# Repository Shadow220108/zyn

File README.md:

<h1 align="center">
<br>

<br>
zyn
<br>
</h1>

<h3 align="center">

A 16 by 8 RGB LED matrix on an ESP32-C3, with a mic, two buttons and USB-C charging!

</h3>

<div align="center">

| Back render |
| --- |
|  |

</div>

## Specs

| | |
| --- | --- |
| Board | 127 x 92 mm, 4 layers |
| Pixels | 128 x SK6812 mini-e, 16 columns by 8 rows, on the bottom side |
| MCU | ESP32-C3-WROOM-02 (4 MB flash, wifi, BLE 5, PCB antenna) |
| Mic | ICS-43434 on I2S (wired, not used by the firmware yet) |
| Charger | MCP73831, 1S LiPo, 500 mA, JST PH connector |
| Regulator | AP2112K-3.3 for the logic |
| Matrix supply | VLED, from VSYS through a p-channel load switch, enabled by IO4 |
| Inputs | BTN_A (boot), BTN_B, reset |
| Status | red charge LED (D2), blue LED on IO8 (D3) |

## How it works

USB-C comes in through a 2A polyfuse (F1). The charger takes VBUS and charges the LiPo, and VSYS feeds the 3.3 V regulator and the matrix switch. The matrix only gets power when IO4 is high, so the board can switch the LEDs off when it's idle.

The data line runs from IO10 through an SN74LV1T125 level shifter (powered from VLED, so the pixels get a logic level they can read) and a 33 ohm series resistor, into the first pixel's DIN. The 128 pixels are chained DIN to DOUT in a snake: row 0 runs left to right, row 1 runs right to left, and so on.

## Pinout

| GPIO | Module pin | Net | Used for |
| --- | --- | --- | --- |
| IO10 | 10 | LED_DATA | pixel data (through the level shifter) |
| IO4 | 3 | LED_EN | matrix power on/off |
| IO9 | 8 | BTN_A | boot button, cycles effects |
| GPIO20 (RXD) | 11 | BTN_B | user button, cycles brightness |
| IO8 | 7 | IO8_LED | blue status LED (D3) |
| IO5 / IO6 / IO7 | 4 / 5 / 6 | MIC_WS / MIC_SCK / MIC_SD | mic (I2S, not used yet) |
| IO18 / IO19 | 13 / 14 | USB_D- / USB_D+ | native USB |
| IO3 / IO1 | 15 / 17 | CC2_SENSE / CC1_SENSE | USB-C orientation sense |
| IO0 | 18 | VBAT_SENSE | battery voltage sense |
| IO2 | 16 | IO2 | spare |

## Firmware

The firmware is in [firmware/zyn/zyn.ino](firmware/zyn/zyn.ino). It was written with help from AI. The pins were checked against the netlist and the module pin layout, but this exact file has not been run on the board yet, so test it with the matrix at low brightness first.

### Setup

1. Arduino IDE, Preferences, add the ESP32 board manager URL `https://espressif.github.io/arduino-esp32/package_esp32_index.json`
2. Boards Manager: install "esp32" by Espressif
3. Library Manager: install "FastLED"
4. Board: "ESP32C3 Dev Module", and turn on "USB CDC on boot" if you want serial output
5. Hold BOOT while plugging in the first time, then upload `zyn.ino`

### Controls

| Button | Action |
| --- | --- |
| BTN_A (boot) | cycle effects: rainbow, scan line, sparkle, breathe |
| BTN_B | cycle brightness: low, medium, high |

The status LED blinks once a second while the firmware is running.

### Notes

- The matrix runs from VSYS, so on battery the pixels see 3.0 to 4.2 V. The brightness is capped at 50 and the power limit is set to 400 mA in the code. Check the pixels at battery voltage before you go higher.
- The chain order and the pixel grid come from the netlist and the position file, so every pixel is in the right place for the effects.
- The mic is wired but the firmware doesn't read it yet.

## Schematic

<div align="center">

| Schematic overview |
| --- |
|  |

</div>

## PCB

<div align="center">

| Full board |
| --- |
|  |

</div>

## How can you get one?

All the files you need are in the `production` folder. Upload `production/zyn.zip` to any PCB fab, and use `production/zyn_bom.csv` and the position files for assembly. The full build log is in [JOURNAL.md](JOURNAL.md).

## BOM

Full part list with LCSC part numbers is in [BOM.csv](BOM.csv) and [production/zyn_bom.csv](production/zyn_bom.csv).

| Designator | Footprint | Qty | Value | LCSC part | Unit price (INR) | Line total (INR) |
| --- | --- | --- | --- | --- | --- | --- |
| C1, C2 | 0603 | 2 | 4.7u/10V | CL10A475KO8NNNC | 10 | 20 |
| C10, C4, C6 | 0402 | 3 | 1u/10V | CL05A105KP5NNNC | 2 | 6 |
| C101 to C228 | 0402 | 132 | 100n/16V | CL05B104KO5NNNC | 1 | 132 |
| C12 | 0402 | 1 | 47n/16V | CL05B473KO5NNNC | 2 | 2 |
| C13, C14 | 1206 | 2 | 47u/10V | CL31A476MPHNNNE | 25 | 50 |
| C15, C16, C3, C5 | 0805 | 4 | 22u/10V | CL21A226MPQNNNE | 12 | 48 |
| C8 | 0603 | 1 | 10u/10V | CL10A106KP8NNNC | 5 | 5 |
| D1 | D_SMA | 1 | SS34 | SS34 (3 A / 40 V) | 10 | 10 |
| D2 | 0603 | 1 | RED (charging) | KT-0603R | 3 | 3 |
| D3 | 0603 | 1 | BLUE (IO8) | KT-0603B | 3 | 3 |
| D101 to D228 | SK6812MINI-E reverse mount | 128 | SK6812MINI-E | SK6812MINI-E | 20 | 2560 |
| F1 | 1812 | 1 | 2A | Bourns MF-MSMF200-2 | 15 | 15 |
| J1 | USB-C HRO TYPE-C-31-M-12 | 1 | USB-C | HRO TYPE-C-31-M-12 | 25 | 25 |
| J2 | JST PH S2B-PH-SM4-TB | 1 | LiPo 1S (JST-PH) | JST S2B-PH-SM4-TB | 10 | 10 |
| Q1, Q2 | SOT-23 | 2 | AO3401A | AO3401A | 15 | 30 |
| Q3 | SOT-23 | 1 | 2N7002 | 2N7002 | 3 | 3 |
| R1, R2 | 0402 | 2 | 5.1k | RC0402FR-075K1L | 1 | 2 |
| R10, R11, R12, R13, R14, R17, R3, R4 | 0402 | 8 | 10k | RC0402FR-0710KL | 1 | 8 |
| R15, R6 | 0402 | 2 | 1k | RC0402FR-071KL | 1 | 2 |
| R16, R18, R19, R21, R7, R8, R9 | 0402 | 7 | 100k | RC0402FR-07100KL | 1 | 7 |
| R20 | 0402 | 1 | 33R | RC0402FR-0733RL | 1 | 1 |
| R5 | 0402 | 1 | 2k | RC0402FR-072KL | 1 | 1 |
| SW1 | SW_SPDT_Shouhan_MSK12C02 | 1 | POWER (slide) | Shouhan MSK12C02 | 25 | 25 |
| SW2 | SW_SPST_PTS810 | 1 | RESET | C&K PTS810SJM250SMTRLFS | 10 | 10 |
| SW3, SW4 | SW_Push Alps SKRTLAE010 | 2 | BTN_A / BTN_B | Alps SKRTLAE010 | 15 | 30 |
| U1 | ESP32-C3-WROOM-02 | 1 | ESP32-C3-WROOM-02 | ESP32-C3-WROOM-02-N4 | 180 | 180 |
| U2 | ICS-43434 | 1 | ICS-43434 | ICS-43434 | 150 | 150 |
| U3 | SOT-23-5 | 1 | MCP73831-2-OT | MCP73831T-2ACI/OT | 25 | 25 |
| U4 | SOT-23-5 | 1 | AP2112K-3.3 | AP2112K-3.3TRG1 | 12 | 12 |
| U5 | SOT-23-5 | 1 | SN74LV1T125DBV | SN74LV1T125DBVR | 15 | 15 |
| U6 | SOT-23-6 | 1 | USBLC6-2SC6 | USBLC6-2SC6 | 10 | 10 |
| **Total** | | | | | | **3400** |

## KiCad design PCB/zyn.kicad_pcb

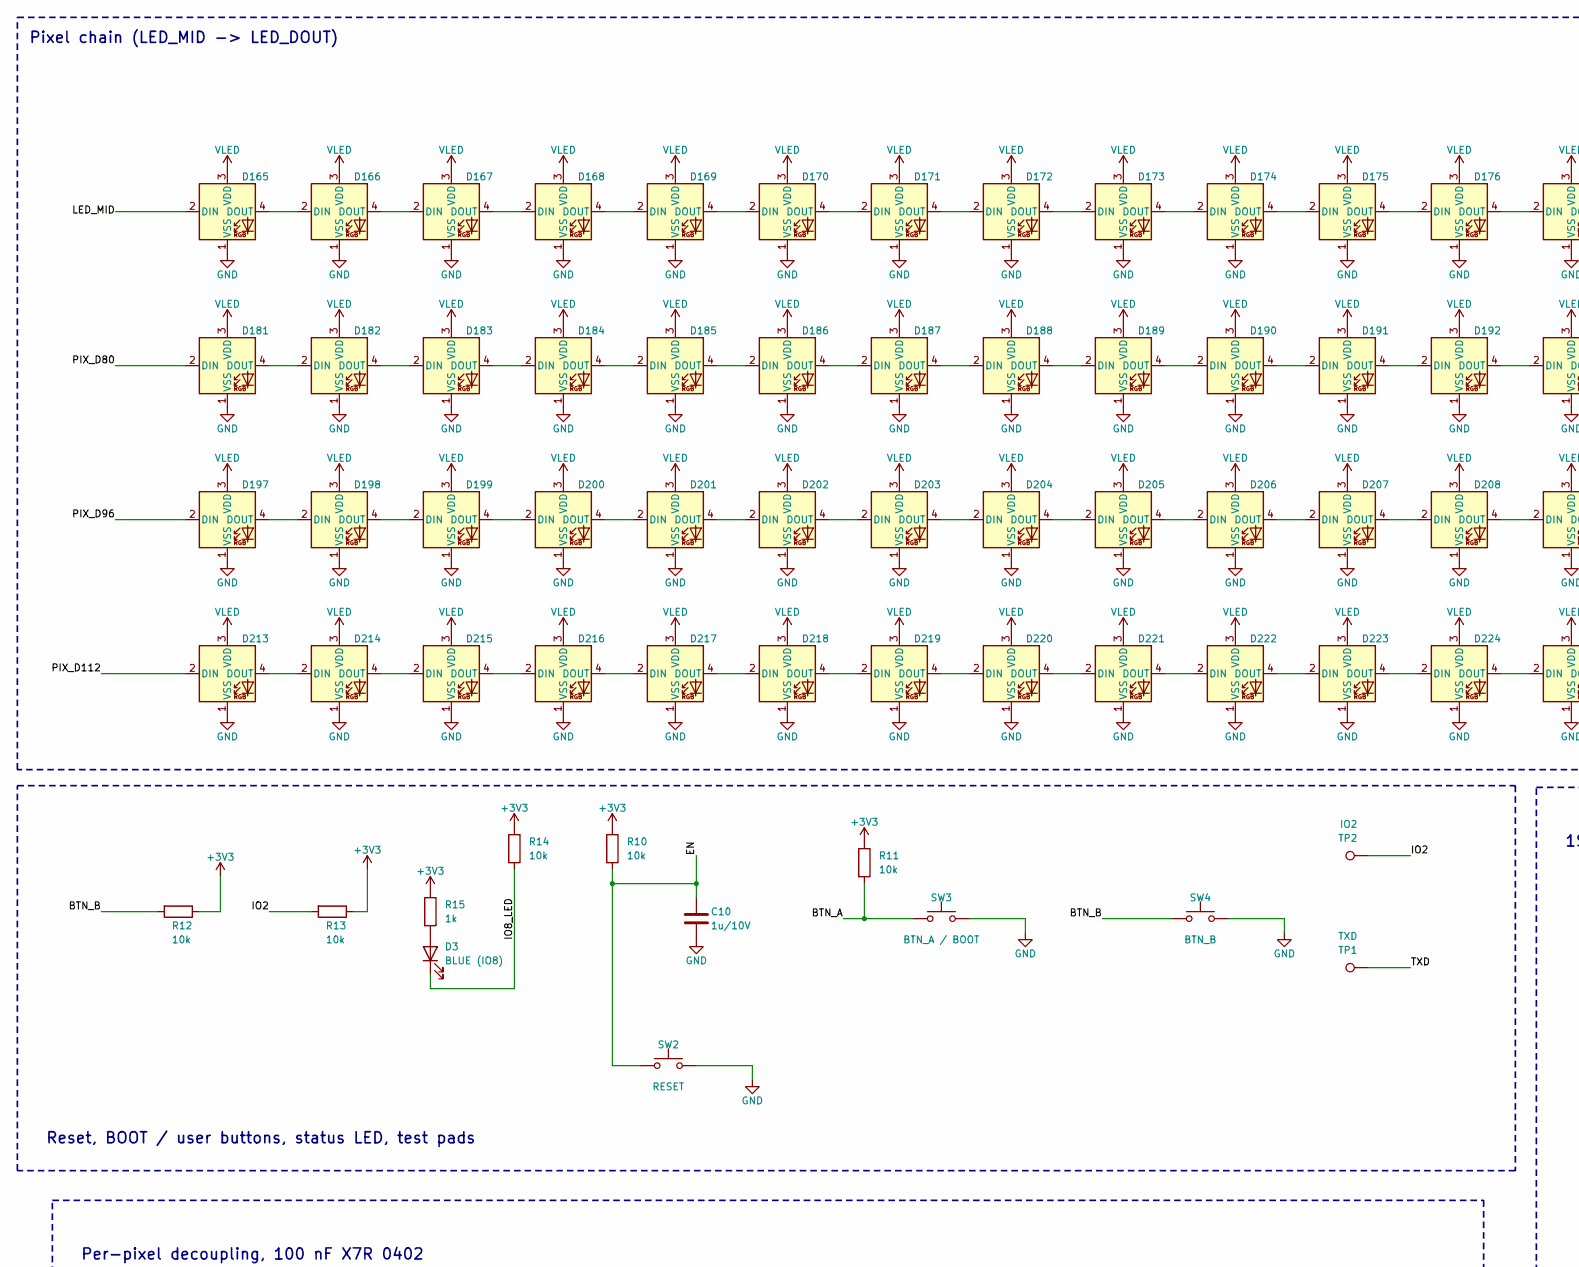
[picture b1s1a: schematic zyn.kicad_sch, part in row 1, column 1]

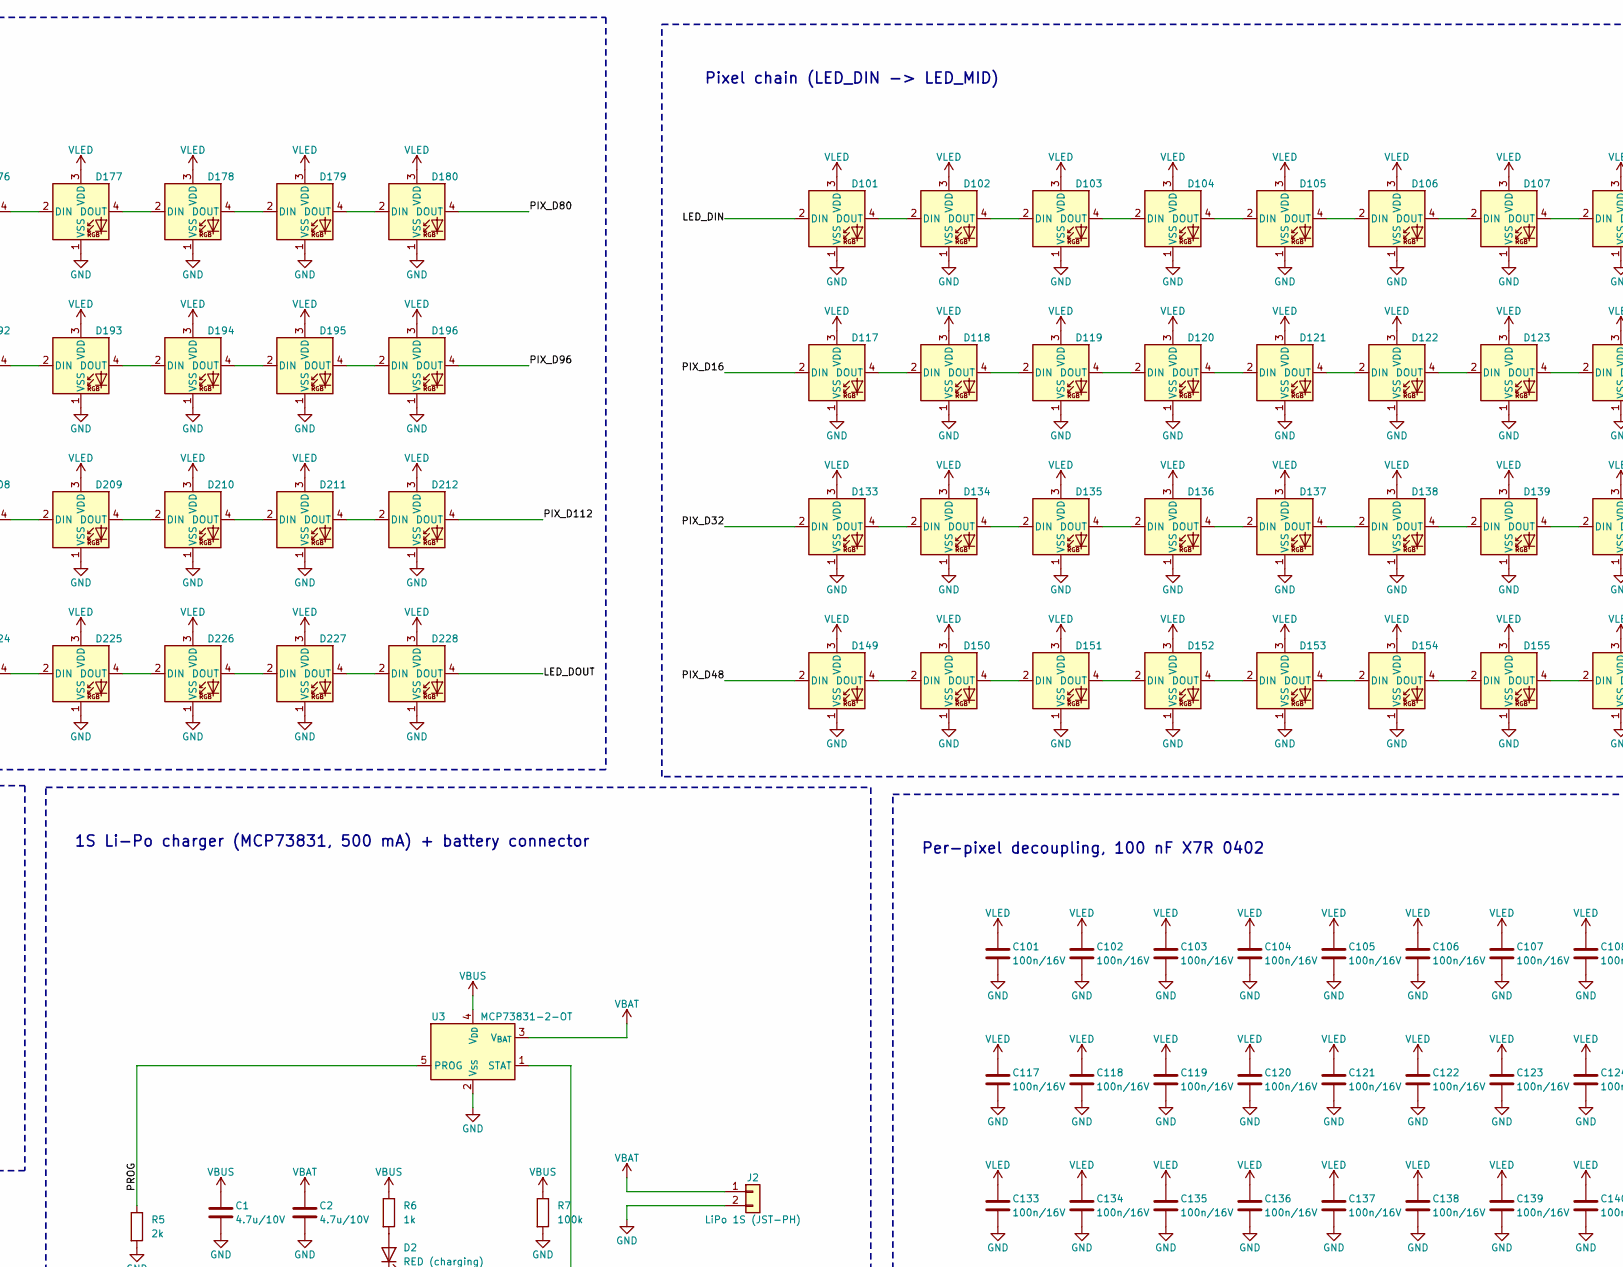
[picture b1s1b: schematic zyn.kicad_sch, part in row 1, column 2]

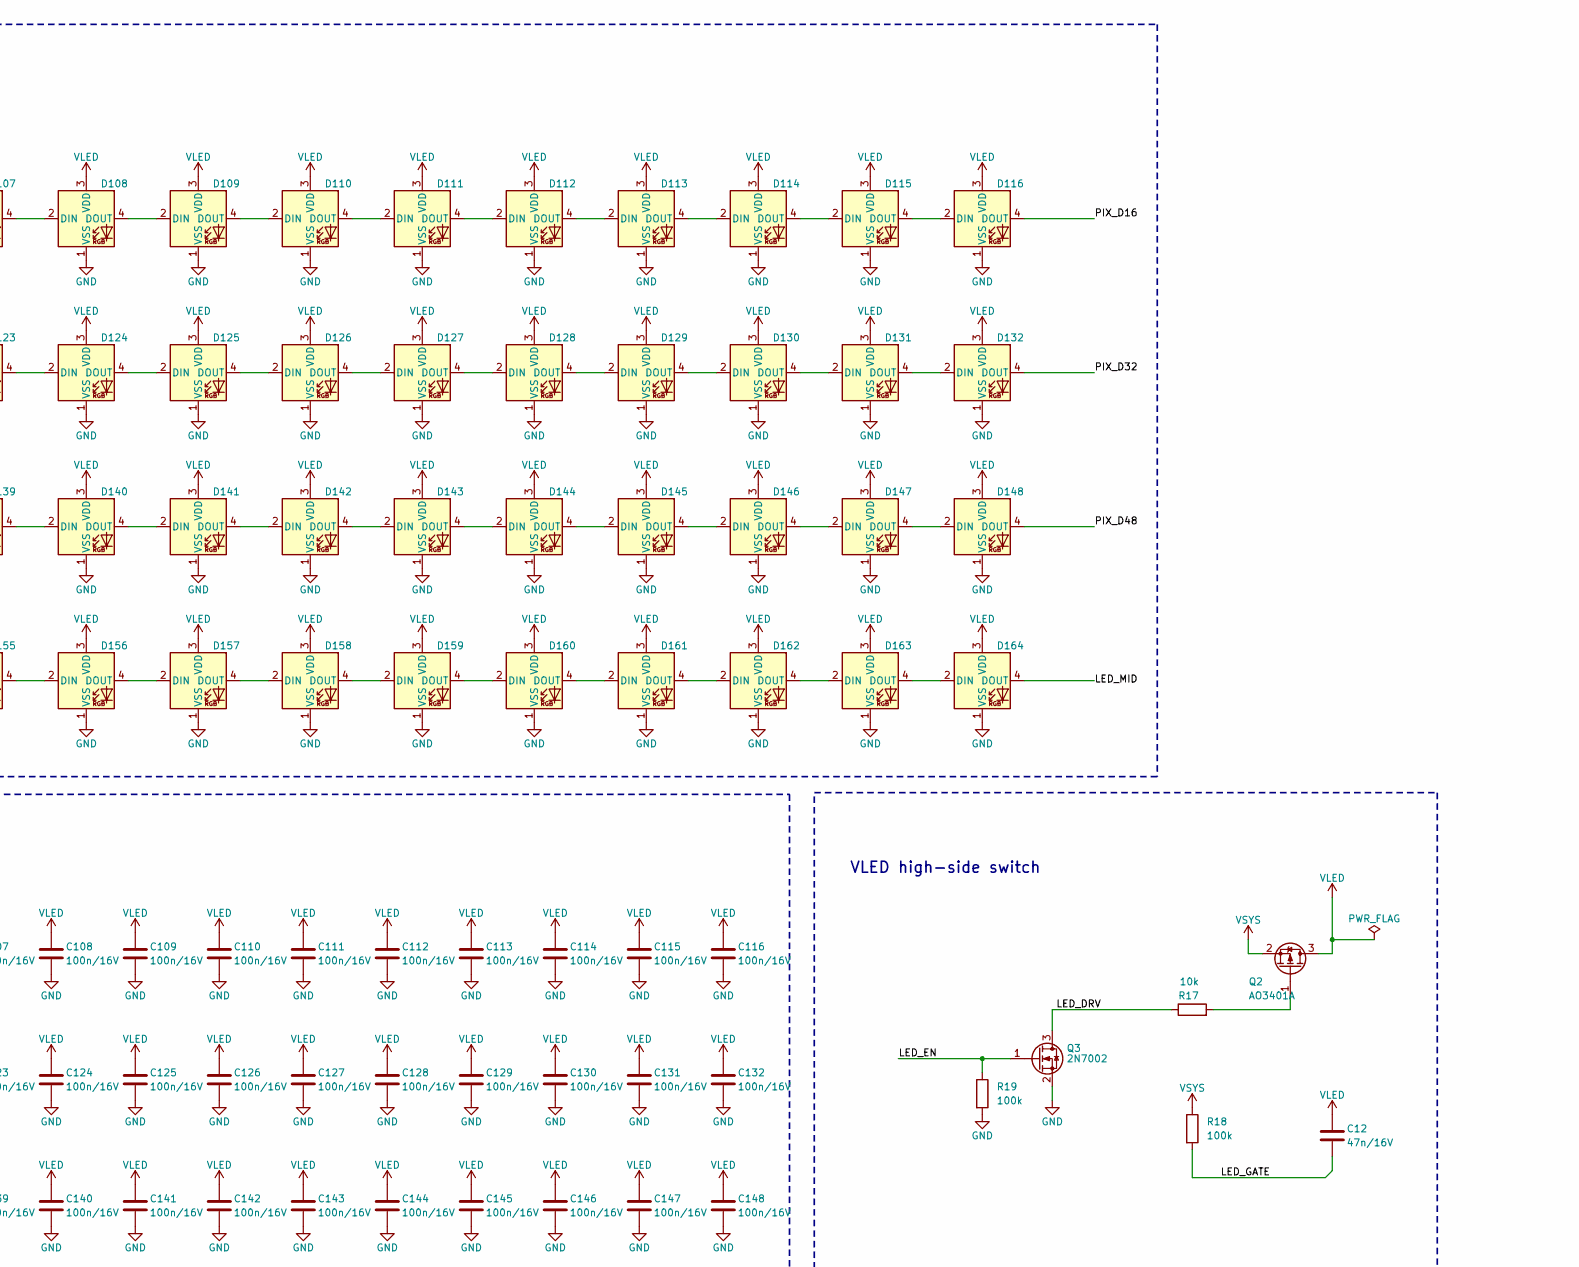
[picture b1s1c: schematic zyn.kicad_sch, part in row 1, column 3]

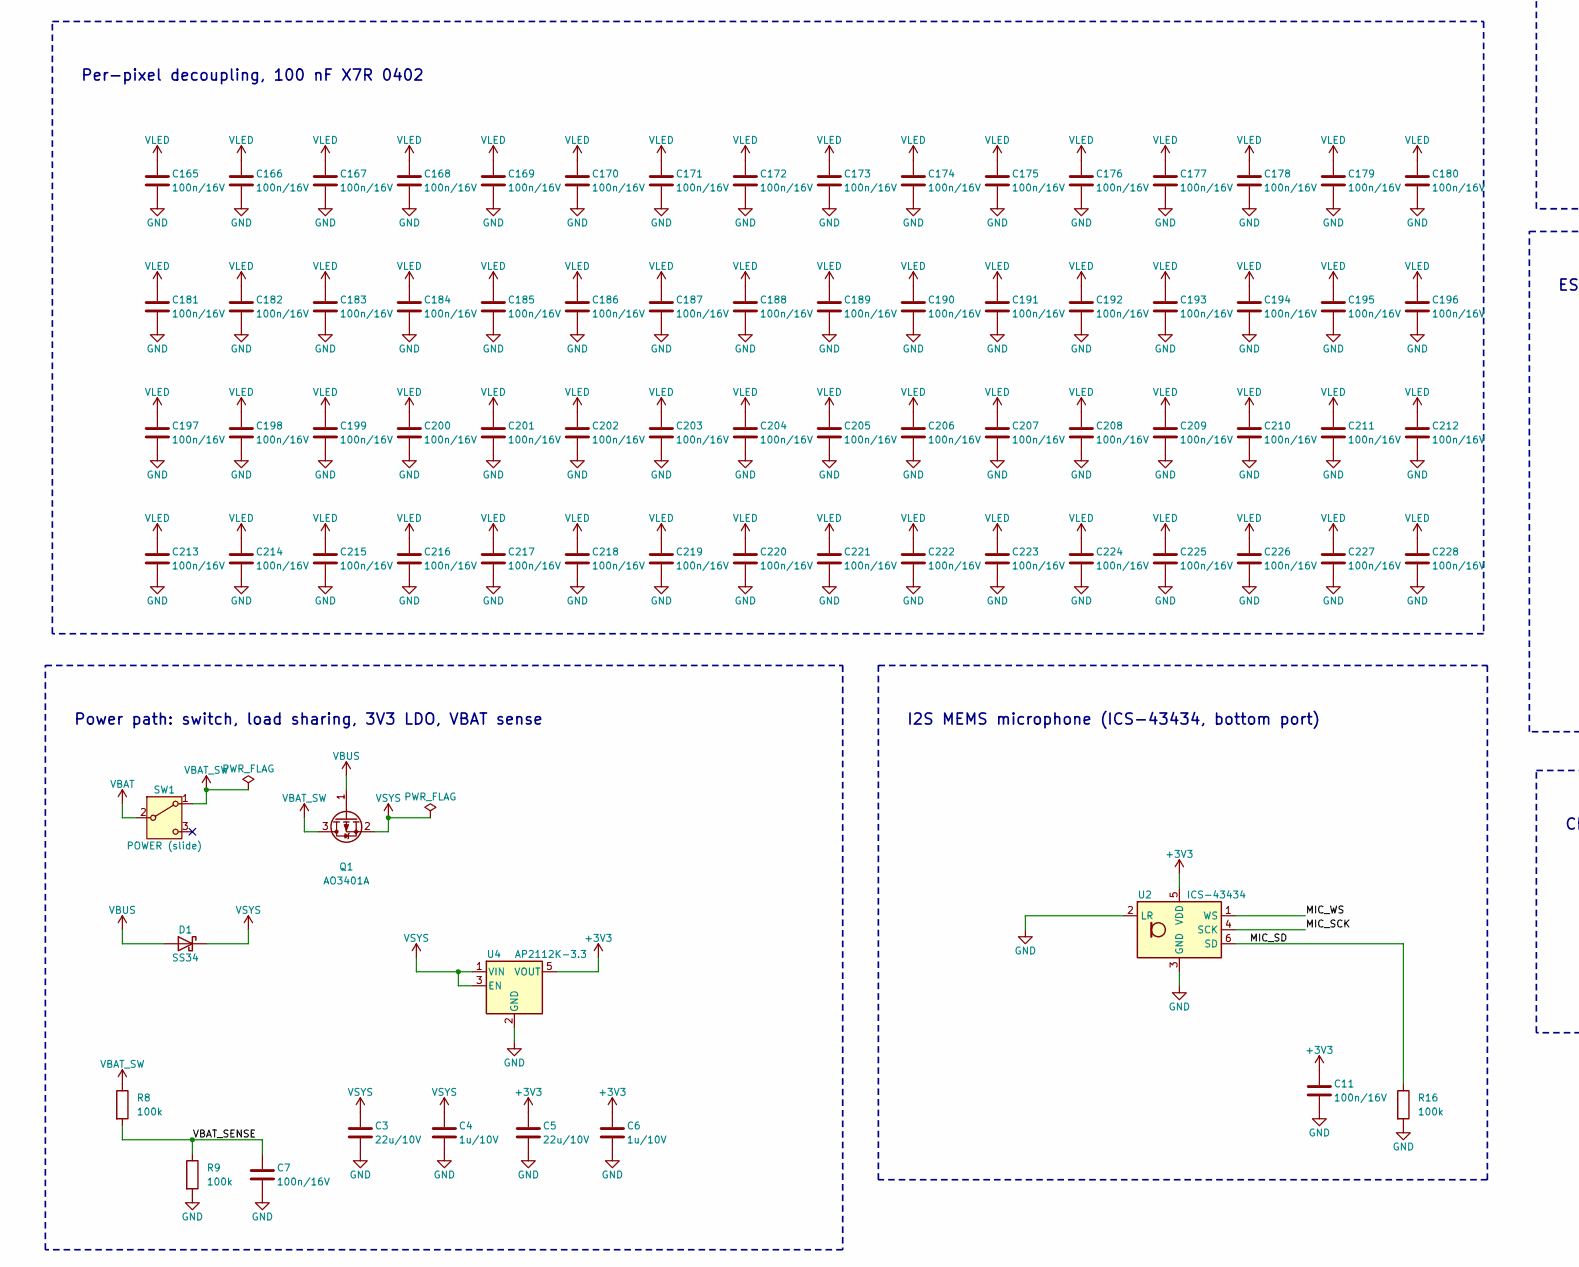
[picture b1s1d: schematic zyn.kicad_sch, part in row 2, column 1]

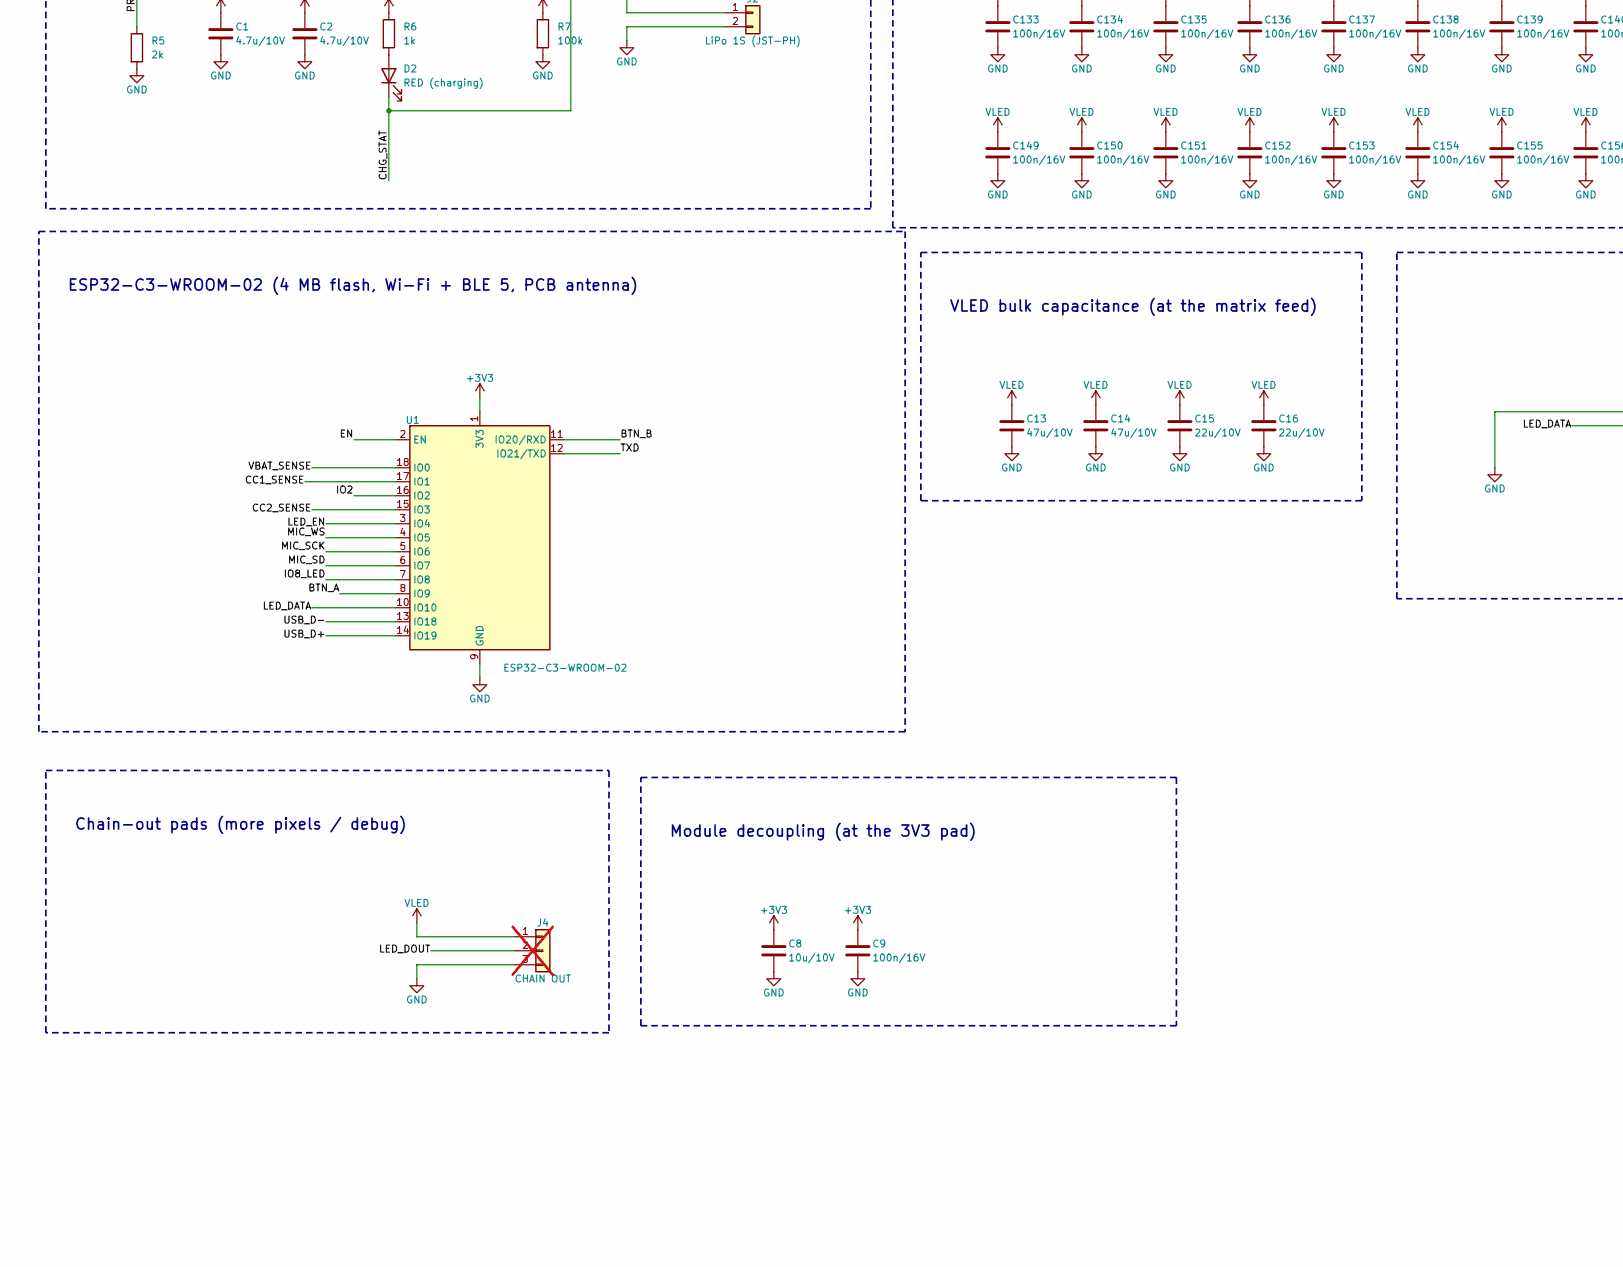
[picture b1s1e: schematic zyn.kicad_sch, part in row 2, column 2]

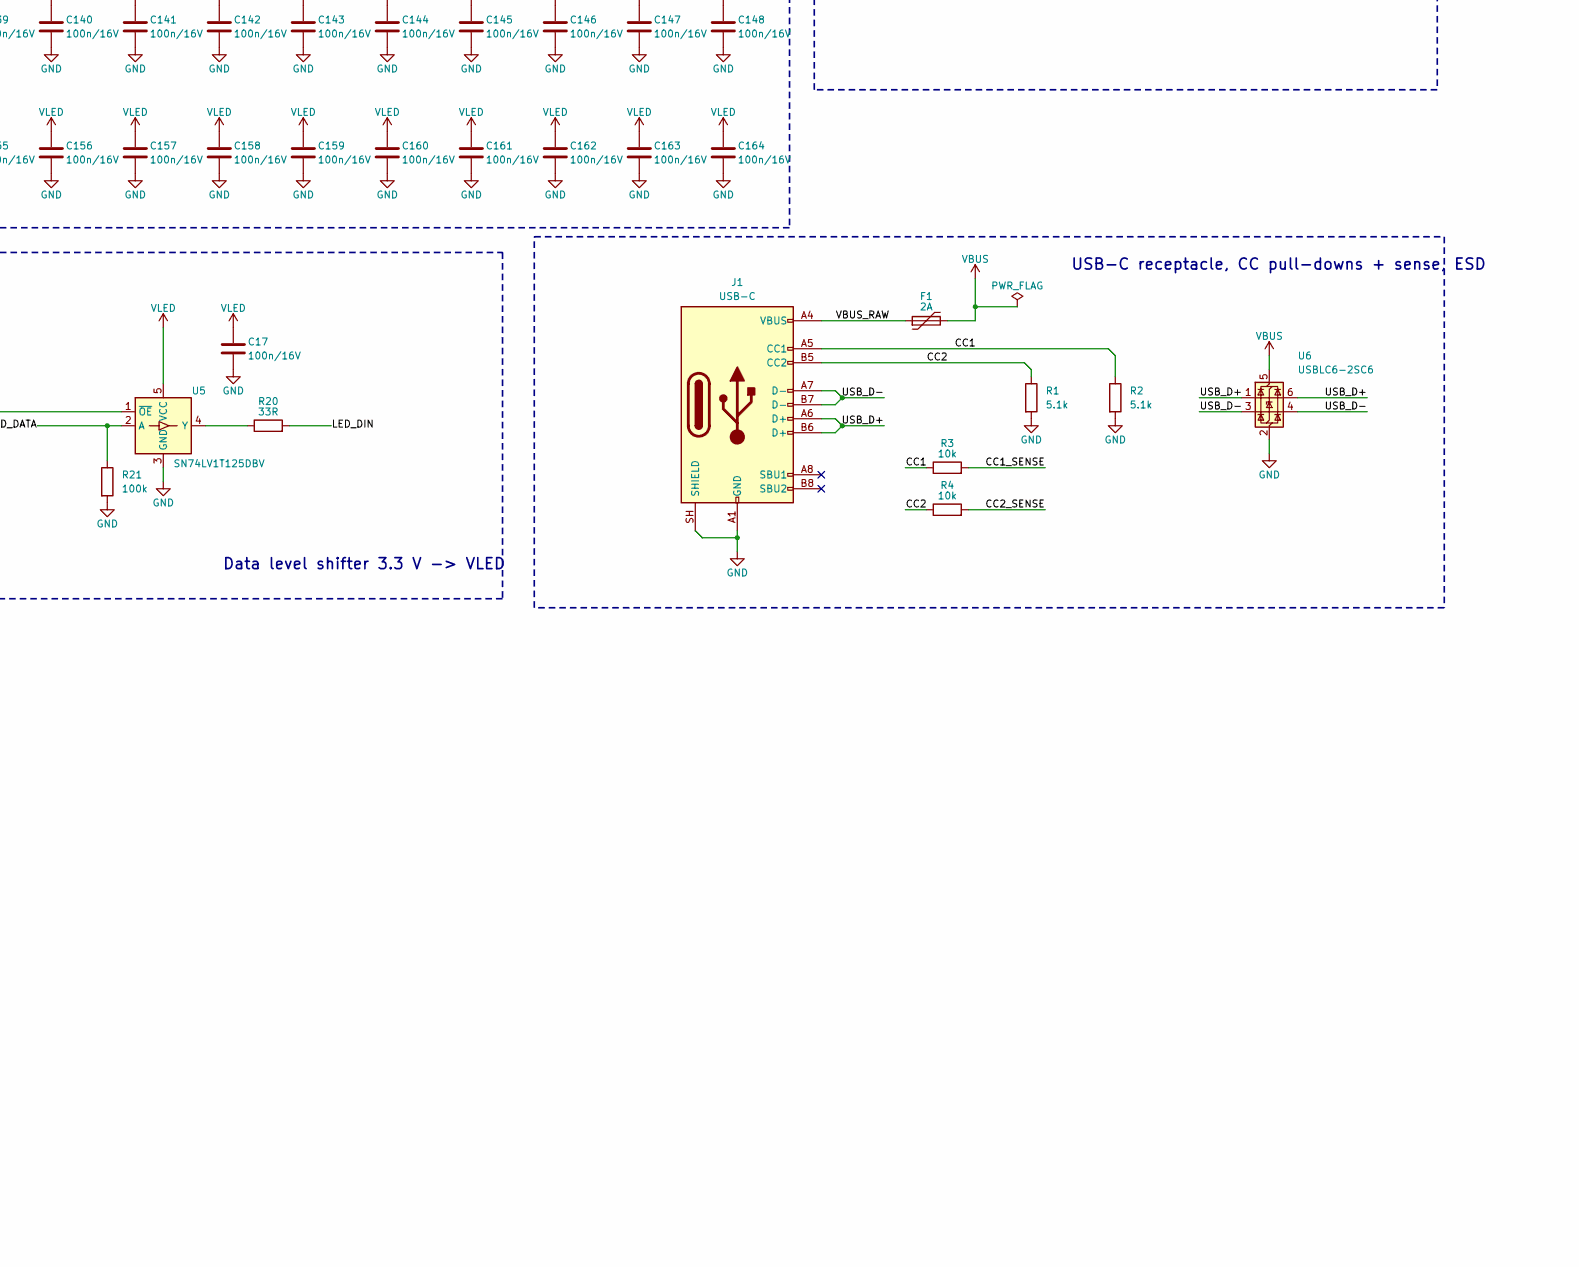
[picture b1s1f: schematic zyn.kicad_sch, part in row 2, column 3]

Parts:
C1, C2: 4.7u/10V; C_0603_1608Metric; MPN CL10A475KO8NNNC
C3, C5, C15, C16: 22u/10V; C_0805_2012Metric; MPN CL21A226MPQNNNE
C4, C6, C10: 1u/10V; C_0402_1005Metric; MPN CL05A105KP5NNNC
C7, C9, C11, C17, C101, C102, C103, C104, C105, C106, C107, C108, C109, C110, C111, C112, C113, C114, C115, C116, C117, C118, C119, C120, C121, C122, C123, C124, C125, C126, C127, C128, C129, C130, C131, C132, C133, C134, C135, C136, C137, C138, C139, C140, C141, C142, C143, C144, C145, C146, C147, C148, C149, C150, C151, C152, C153, C154, C155, C156, C157, C158, C159, C160, C161, C162, C163, C164, C165, C166, C167, C168, C169, C170, C171, C172, C173, C174, C175, C176, C177, C178, C179, C180, C181, C182, C183, C184, C185, C186, C187, C188, C189, C190, C191, C192, C193, C194, C195, C196, C197, C198, C199, C200, C201, C202, C203, C204, C205, C206, C207, C208, C209, C210, C211, C212, C213, C214, C215, C216, C217, C218, C219, C220, C221, C222, C223, C224, C225, C226, C227, C228: 100n/16V; C_0402_1005Metric; MPN CL05B104KO5NNNC
C8: 10u/10V; C_0603_1608Metric; MPN CL10A106KP8NNNC
C12: 47n/16V; C_0402_1005Metric; MPN CL05B473KO5NNNC
C13, C14: 47u/10V; C_1206_3216Metric; MPN CL31A476MPHNNNE
D1: SS34; D_SMA; MPN SS34 (3 A / 40 V)
D2: RED (charging); LED_0603_1608Metric; MPN KT-0603R
D3: BLUE (IO8); LED_0603_1608Metric; MPN KT-0603B
D101, D102, D103, D104, D105, D106, D107, D108, D109, D110, D111, D112, D113, D114, D115, D116, D117, D118, D119, D120, D121, D122, D123, D124, D125, D126, D127, D128, D129, D130, D131, D132, D133, D134, D135, D136, D137, D138, D139, D140, D141, D142, D143, D144, D145, D146, D147, D148, D149, D150, D151, D152, D153, D154, D155, D156, D157, D158, D159, D160, D161, D162, D163, D164, D165, D166, D167, D168, D169, D170, D171, D172, D173, D174, D175, D176, D177, D178, D179, D180, D181, D182, D183, D184, D185, D186, D187, D188, D189, D190, D191, D192, D193, D194, D195, D196, D197, D198, D199, D200, D201, D202, D203, D204, D205, D206, D207, D208, D209, D210, D211, D212, D213, D214, D215, D216, D217, D218, D219, D220, D221, D222, D223, D224, D225, D226, D227, D228: SK6812MINI-E; LED_SK6812MINI-E_3.2x2.8mm_P1.5mm_ReverseMount; MPN SK6812MINI-E
F1: 2A; Fuse_1812_4532Metric; MPN Bourns MF-MSMF200-2 (1812, 2 A hold)
J1: USB-C; USB_C_Receptacle_HRO_TYPE-C-31-M-12; MPN HRO TYPE-C-31-M-12
J2: LiPo 1S (JST-PH); JST_PH_S2B-PH-SM4-TB_1x02-1MP_P2.00mm_Horizontal; MPN JST S2B-PH-SM4-TB
J4: CHAIN OUT; PinHeader_1x03_P2.54mm_Vertical; MPN 2.54 mm 1x3 header (DNP); not fitted
Q1, Q2: AO3401A; SOT-23; MPN AO3401A
Q3: 2N7002; SOT-23; MPN 2N7002
R1, R2: 5.1k; R_0402_1005Metric; MPN RC0402FR-075K1L
R3, R4, R10, R11, R12, R13, R14, R17: 10k; R_0402_1005Metric; MPN RC0402FR-0710KL
R5: 2k; R_0402_1005Metric; MPN RC0402FR-072KL
R6, R15: 1k; R_0402_1005Metric; MPN RC0402FR-071KL
R7, R8, R9, R16, R18, R19, R21: 100k; R_0402_1005Metric; MPN RC0402FR-07100KL
R20: 33R; R_0402_1005Metric; MPN RC0402FR-0733RL
SW1: POWER (slide); SW_SPDT_Shouhan_MSK12C02; MPN Shouhan MSK12C02
SW2: RESET; SW_SPST_PTS810; MPN C&K PTS810SJM250SMTRLFS
SW3: BTN_A / BOOT; SW_Push_1P1T-MP_NO_Horizontal_Alps_SKRTLAE010; MPN Alps SKRTLAE010
SW4: BTN_B; SW_Push_1P1T-MP_NO_Horizontal_Alps_SKRTLAE010; MPN Alps SKRTLAE010
TP1: TXD; TestPoint_Pad_D1.5mm
TP2: IO2; TestPoint_Pad_D1.5mm
U1: ESP32-C3-WROOM-02; MPN ESP32-C3-WROOM-02-N4
U2: ICS-43434; InvenSense_ICS-43434-6_3.5x2.65mm; MPN ICS-43434
U3: MCP73831-2-OT; SOT-23-5; MPN MCP73831T-2ACI/OT
U4: AP2112K-3.3; SOT-23-5; MPN AP2112K-3.3TRG1
U5: SN74LV1T125DBV; SOT-23-5; MPN SN74LV1T125DBVR
U6: USBLC6-2SC6; SOT-23-6; MPN USBLC6-2SC6

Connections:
+3V3: C5.1, C6.1, C8.1, C9.1, C11.1, R10.1, R11.1, R12.1, R13.1, R14.1, R15.1, U1.1 (3V3), U2.5 (VDD), U4.5 (VOUT)
/BTN_A: R11.2, SW3.1, U1.8 (IO9)
/BTN_B: R12.2, SW4.1, U1.11 (IO20/RXD)
/CC1_SENSE: R3.2, U1.17 (IO1)
/CC2_SENSE: R4.2, U1.15 (IO3)
/CHG_STAT: D2.1 (K), U3.1 (STAT)
/EN: C10.1, R10.2, SW2.1, U1.2 (EN)
/IO2: R13.2, TP2.1 (1_1), U1.16 (IO2)
/IO8_LED: D3.1 (K), R14.2, U1.7 (IO8)
/LED_DATA: R21.1, U1.10 (IO10), U5.2 (A)
/LED_DIN: D101.2 (DIN), R20.2
/LED_DOUT: D228.4 (DOUT), J4.2
/LED_EN: Q3.1 (G), R19.1, U1.3 (IO4)
/LED_GATE: C12.2, R18.2
/LED_MID: D164.4 (DOUT), D165.2 (DIN)
/MIC_SCK: U1.5 (IO6), U2.4 (SCK)
/MIC_SD: R16.1, U1.6 (IO7), U2.6 (SD)
/MIC_WS: U1.4 (IO5), U2.1 (WS)
/PIX_D16: D116.4 (DOUT), D117.2 (DIN)
/PIX_D32: D132.4 (DOUT), D133.2 (DIN)
/PIX_D48: D148.4 (DOUT), D149.2 (DIN)
/PIX_D80: D180.4 (DOUT), D181.2 (DIN)
/PIX_D96: D196.4 (DOUT), D197.2 (DIN)
/PIX_D112: D212.4 (DOUT), D213.2 (DIN)
/PROG: R5.1, U3.5 (PROG)
/TXD: TP1.1 (1_1), U1.12 (IO21/TXD)
/VBAT_SENSE: C7.1, R8.2, R9.1, U1.18 (IO0)
/VBUS_RAW: F1.1, J1.A4 (VBUS), J1.A9 (VBUS), J1.B4 (VBUS), J1.B9 (VBUS)
GND: C1.2, C2.2, C3.2, C4.2, C5.2, C6.2, C7.2, C8.2, C9.2, C10.2, C11.2, C13.2, C14.2, C15.2, C16.2, C17.2, C101.2, C102.2, C103.2, C104.2, C105.2, C106.2, C107.2, C108.2, C109.2, C110.2, C111.2, C112.2, C113.2, C114.2, C115.2, C116.2, C117.2, C118.2, C119.2, C120.2, C121.2, C122.2, C123.2, C124.2, C125.2, C126.2, C127.2, C128.2, C129.2, C130.2, C131.2, C132.2, C133.2, C134.2, C135.2, C136.2, C137.2, C138.2, C139.2, C140.2, C141.2, C142.2, C143.2, C144.2, C145.2, C146.2, C147.2, C148.2, C149.2, C150.2, C151.2, C152.2, C153.2, C154.2, C155.2, C156.2, C157.2, C158.2, C159.2, C160.2, C161.2, C162.2, C163.2, C164.2, C165.2, C166.2, C167.2, C168.2, C169.2, C170.2, C171.2, C172.2, C173.2, C174.2, C175.2, C176.2, C177.2, C178.2, C179.2, C180.2, C181.2, C182.2, C183.2, C184.2, C185.2, C186.2, C187.2, C188.2, C189.2, C190.2, C191.2, C192.2, C193.2, C194.2, C195.2, C196.2, C197.2, C198.2, C199.2, C200.2, C201.2, C202.2, C203.2, C204.2, C205.2, C206.2, C207.2, C208.2, C209.2, C210.2, C211.2, C212.2, C213.2, C214.2, C215.2, C216.2, C217.2, C218.2, C219.2, C220.2, C221.2, C222.2, C223.2, C224.2, C225.2, C226.2, C227.2, C228.2, D101.1 (VSS), D102.1 (VSS), D103.1 (VSS), D104.1 (VSS), D105.1 (VSS), D106.1 (VSS), D107.1 (VSS), D108.1 (VSS), D109.1 (VSS), D110.1 (VSS), D111.1 (VSS), D112.1 (VSS), D113.1 (VSS), D114.1 (VSS), D115.1 (VSS), D116.1 (VSS), D117.1 (VSS), D118.1 (VSS), D119.1 (VSS), D120.1 (VSS), D121.1 (VSS), D122.1 (VSS), D123.1 (VSS), D124.1 (VSS), D125.1 (VSS), D126.1 (VSS), D127.1 (VSS), D128.1 (VSS), D129.1 (VSS), D130.1 (VSS), D131.1 (VSS), D132.1 (VSS), D133.1 (VSS), D134.1 (VSS), D135.1 (VSS), D136.1 (VSS), D137.1 (VSS), D138.1 (VSS), D139.1 (VSS), D140.1 (VSS), D141.1 (VSS), D142.1 (VSS), D143.1 (VSS), D144.1 (VSS), D145.1 (VSS), D146.1 (VSS), D147.1 (VSS), D148.1 (VSS), D149.1 (VSS), D150.1 (VSS), D151.1 (VSS), D152.1 (VSS), D153.1 (VSS), D154.1 (VSS), D155.1 (VSS), D156.1 (VSS), D157.1 (VSS), D158.1 (VSS), D159.1 (VSS), D160.1 (VSS), D161.1 (VSS), D162.1 (VSS), D163.1 (VSS), D164.1 (VSS), D165.1 (VSS), D166.1 (VSS), D167.1 (VSS), D168.1 (VSS), D169.1 (VSS), D170.1 (VSS), D171.1 (VSS), D172.1 (VSS), D173.1 (VSS), D174.1 (VSS), D175.1 (VSS), D176.1 (VSS), D177.1 (VSS), D178.1 (VSS), D179.1 (VSS), D180.1 (VSS), D181.1 (VSS), D182.1 (VSS), D183.1 (VSS), D184.1 (VSS), D185.1 (VSS), D186.1 (VSS), D187.1 (VSS), D188.1 (VSS), D189.1 (VSS), D190.1 (VSS), D191.1 (VSS), D192.1 (VSS), D193.1 (VSS), D194.1 (VSS), D195.1 (VSS), D196.1 (VSS), D197.1 (VSS), D198.1 (VSS), D199.1 (VSS), D200.1 (VSS), D201.1 (VSS), D202.1 (VSS), D203.1 (VSS), D204.1 (VSS), D205.1 (VSS), D206.1 (VSS), D207.1 (VSS), D208.1 (VSS), D209.1 (VSS), D210.1 (VSS), D211.1 (VSS), D212.1 (VSS), D213.1 (VSS), D214.1 (VSS), D215.1 (VSS), D216.1 (VSS), D217.1 (VSS), D218.1 (VSS), D219.1 (VSS), D220.1 (VSS), D221.1 (VSS), D222.1 (VSS), D223.1 (VSS), D224.1 (VSS), D225.1 (VSS), D226.1 (VSS), D227.1 (VSS), D228.1 (VSS), J1.A1 (GND), J1.A12 (GND), J1.B1 (GND), J1.B12 (GND), J1.SH (SHIELD), J2.2, J4.3, Q3.2 (S), R1.2, R2.2, R5.2, R7.2, R9.2, R16.2, R19.2, R21.2, SW2.2, SW3.2, SW4.2, U1.9 (GND), U1.19 (GND), U2.2 (LR), U2.3 (GND), U3.2 (V_{SS}), U4.2 (GND), U5.1 (~OE), U5.3 (GND), U6.2 (GND)
unnamed: D2.2 (A), R6.2
unnamed: D3.2 (A), R15.2
unnamed: D101.4 (DOUT), D102.2 (DIN)
unnamed: D102.4 (DOUT), D103.2 (DIN)
unnamed: D103.4 (DOUT), D104.2 (DIN)
unnamed: D104.4 (DOUT), D105.2 (DIN)
unnamed: D105.4 (DOUT), D106.2 (DIN)
unnamed: D106.4 (DOUT), D107.2 (DIN)
unnamed: D107.4 (DOUT), D108.2 (DIN)
unnamed: D108.4 (DOUT), D109.2 (DIN)
unnamed: D109.4 (DOUT), D110.2 (DIN)
unnamed: D110.4 (DOUT), D111.2 (DIN)
unnamed: D111.4 (DOUT), D112.2 (DIN)
unnamed: D112.4 (DOUT), D113.2 (DIN)
unnamed: D113.4 (DOUT), D114.2 (DIN)
unnamed: D114.4 (DOUT), D115.2 (DIN)
unnamed: D115.4 (DOUT), D116.2 (DIN)
unnamed: D117.4 (DOUT), D118.2 (DIN)
unnamed: D118.4 (DOUT), D119.2 (DIN)
unnamed: D119.4 (DOUT), D120.2 (DIN)
unnamed: D120.4 (DOUT), D121.2 (DIN)
unnamed: D121.4 (DOUT), D122.2 (DIN)
unnamed: D122.4 (DOUT), D123.2 (DIN)
unnamed: D123.4 (DOUT), D124.2 (DIN)
unnamed: D124.4 (DOUT), D125.2 (DIN)
unnamed: D125.4 (DOUT), D126.2 (DIN)
unnamed: D126.4 (DOUT), D127.2 (DIN)
unnamed: D127.4 (DOUT), D128.2 (DIN)
unnamed: D128.4 (DOUT), D129.2 (DIN)
unnamed: D129.4 (DOUT), D130.2 (DIN)
unnamed: D130.4 (DOUT), D131.2 (DIN)
unnamed: D131.4 (DOUT), D132.2 (DIN)
unnamed: D133.4 (DOUT), D134.2 (DIN)
unnamed: D134.4 (DOUT), D135.2 (DIN)
unnamed: D135.4 (DOUT), D136.2 (DIN)
unnamed: D136.4 (DOUT), D137.2 (DIN)
unnamed: D137.4 (DOUT), D138.2 (DIN)
unnamed: D138.4 (DOUT), D139.2 (DIN)
unnamed: D139.4 (DOUT), D140.2 (DIN)
unnamed: D140.4 (DOUT), D141.2 (DIN)
unnamed: D141.4 (DOUT), D142.2 (DIN)
unnamed: D142.4 (DOUT), D143.2 (DIN)
unnamed: D143.4 (DOUT), D144.2 (DIN)
unnamed: D144.4 (DOUT), D145.2 (DIN)
unnamed: D145.4 (DOUT), D146.2 (DIN)
unnamed: D146.4 (DOUT), D147.2 (DIN)
unnamed: D147.4 (DOUT), D148.2 (DIN)
unnamed: D149.4 (DOUT), D150.2 (DIN)
unnamed: D150.4 (DOUT), D151.2 (DIN)
unnamed: D151.4 (DOUT), D152.2 (DIN)
unnamed: D152.4 (DOUT), D153.2 (DIN)
unnamed: D153.4 (DOUT), D154.2 (DIN)
unnamed: D154.4 (DOUT), D155.2 (DIN)
unnamed: D155.4 (DOUT), D156.2 (DIN)
unnamed: D156.4 (DOUT), D157.2 (DIN)
unnamed: D157.4 (DOUT), D158.2 (DIN)
unnamed: D158.4 (DOUT), D159.2 (DIN)
unnamed: D159.4 (DOUT), D160.2 (DIN)
unnamed: D160.4 (DOUT), D161.2 (DIN)
unnamed: D161.4 (DOUT), D162.2 (DIN)
unnamed: D162.4 (DOUT), D163.2 (DIN)
unnamed: D163.4 (DOUT), D164.2 (DIN)
unnamed: D165.4 (DOUT), D166.2 (DIN)
unnamed: D166.4 (DOUT), D167.2 (DIN)
unnamed: D167.4 (DOUT), D168.2 (DIN)
unnamed: D168.4 (DOUT), D169.2 (DIN)
unnamed: D169.4 (DOUT), D170.2 (DIN)
unnamed: D170.4 (DOUT), D171.2 (DIN)
unnamed: D171.4 (DOUT), D172.2 (DIN)
unnamed: D172.4 (DOUT), D173.2 (DIN)
unnamed: D173.4 (DOUT), D174.2 (DIN)
unnamed: D174.4 (DOUT), D175.2 (DIN)
unnamed: D175.4 (DOUT), D176.2 (DIN)
unnamed: D176.4 (DOUT), D177.2 (DIN)
unnamed: D177.4 (DOUT), D178.2 (DIN)
unnamed: D178.4 (DOUT), D179.2 (DIN)
unnamed: D179.4 (DOUT), D180.2 (DIN)
unnamed: D181.4 (DOUT), D182.2 (DIN)
unnamed: D182.4 (DOUT), D183.2 (DIN)
unnamed: D183.4 (DOUT), D184.2 (DIN)
unnamed: D184.4 (DOUT), D185.2 (DIN)
unnamed: D185.4 (DOUT), D186.2 (DIN)
unnamed: D186.4 (DOUT), D187.2 (DIN)
unnamed: D187.4 (DOUT), D188.2 (DIN)
unnamed: D188.4 (DOUT), D189.2 (DIN)
unnamed: D189.4 (DOUT), D190.2 (DIN)
unnamed: D190.4 (DOUT), D191.2 (DIN)
unnamed: D191.4 (DOUT), D192.2 (DIN)
unnamed: D192.4 (DOUT), D193.2 (DIN)
unnamed: D193.4 (DOUT), D194.2 (DIN)
unnamed: D194.4 (DOUT), D195.2 (DIN)
unnamed: D195.4 (DOUT), D196.2 (DIN)
unnamed: D197.4 (DOUT), D198.2 (DIN)
unnamed: D198.4 (DOUT), D199.2 (DIN)
unnamed: D199.4 (DOUT), D200.2 (DIN)
unnamed: D200.4 (DOUT), D201.2 (DIN)
unnamed: D201.4 (DOUT), D202.2 (DIN)
unnamed: D202.4 (DOUT), D203.2 (DIN)
unnamed: D203.4 (DOUT), D204.2 (DIN)
unnamed: D204.4 (DOUT), D205.2 (DIN)
unnamed: D205.4 (DOUT), D206.2 (DIN)
unnamed: D206.4 (DOUT), D207.2 (DIN)
unnamed: D207.4 (DOUT), D208.2 (DIN)
unnamed: D208.4 (DOUT), D209.2 (DIN)
unnamed: D209.4 (DOUT), D210.2 (DIN)
unnamed: D210.4 (DOUT), D211.2 (DIN)
unnamed: D211.4 (DOUT), D212.2 (DIN)
unnamed: D213.4 (DOUT), D214.2 (DIN)
unnamed: D214.4 (DOUT), D215.2 (DIN)
unnamed: D215.4 (DOUT), D216.2 (DIN)
unnamed: D216.4 (DOUT), D217.2 (DIN)
unnamed: D217.4 (DOUT), D218.2 (DIN)
unnamed: D218.4 (DOUT), D219.2 (DIN)
unnamed: D219.4 (DOUT), D220.2 (DIN)
unnamed: D220.4 (DOUT), D221.2 (DIN)
unnamed: D221.4 (DOUT), D222.2 (DIN)
unnamed: D222.4 (DOUT), D223.2 (DIN)
unnamed: D223.4 (DOUT), D224.2 (DIN)
unnamed: D224.4 (DOUT), D225.2 (DIN)
unnamed: D225.4 (DOUT), D226.2 (DIN)
unnamed: D226.4 (DOUT), D227.2 (DIN)
unnamed: D227.4 (DOUT), D228.2 (DIN)
unnamed: R20.1, U5.4 (Y)
VBAT: C2.1, J2.1, SW1.2 (B), U3.3 (V_{BAT})
VBAT_SW: Q1.3 (D), R8.1, SW1.1 (A)
VBUS: C1.1, D1.2 (A), F1.2, Q1.1 (G), R6.1, R7.1, U3.4 (V_{DD}), U6.5 (VBUS)
VLED: C12.1, C13.1, C14.1, C15.1, C16.1, C17.1, C101.1, C102.1, C103.1, C104.1, C105.1, C106.1, C107.1, C108.1, C109.1, C110.1, C111.1, C112.1, C113.1, C114.1, C115.1, C116.1, C117.1, C118.1, C119.1, C120.1, C121.1, C122.1, C123.1, C124.1, C125.1, C126.1, C127.1, C128.1, C129.1, C130.1, C131.1, C132.1, C133.1, C134.1, C135.1, C136.1, C137.1, C138.1, C139.1, C140.1, C141.1, C142.1, C143.1, C144.1, C145.1, C146.1, C147.1, C148.1, C149.1, C150.1, C151.1, C152.1, C153.1, C154.1, C155.1, C156.1, C157.1, C158.1, C159.1, C160.1, C161.1, C162.1, C163.1, C164.1, C165.1, C166.1, C167.1, C168.1, C169.1, C170.1, C171.1, C172.1, C173.1, C174.1, C175.1, C176.1, C177.1, C178.1, C179.1, C180.1, C181.1, C182.1, C183.1, C184.1, C185.1, C186.1, C187.1, C188.1, C189.1, C190.1, C191.1, C192.1, C193.1, C194.1, C195.1, C196.1, C197.1, C198.1, C199.1, C200.1, C201.1, C202.1, C203.1, C204.1, C205.1, C206.1, C207.1, C208.1, C209.1, C210.1, C211.1, C212.1, C213.1, C214.1, C215.1, C216.1, C217.1, C218.1, C219.1, C220.1, C221.1, C222.1, C223.1, C224.1, C225.1, C226.1, C227.1, C228.1, D101.3 (VDD), D102.3 (VDD), D103.3 (VDD), D104.3 (VDD), D105.3 (VDD), D106.3 (VDD), D107.3 (VDD), D108.3 (VDD), D109.3 (VDD), D110.3 (VDD), D111.3 (VDD), D112.3 (VDD), D113.3 (VDD), D114.3 (VDD), D115.3 (VDD), D116.3 (VDD), D117.3 (VDD), D118.3 (VDD), D119.3 (VDD), D120.3 (VDD), D121.3 (VDD), D122.3 (VDD), D123.3 (VDD), D124.3 (VDD), D125.3 (VDD), D126.3 (VDD), D127.3 (VDD), D128.3 (VDD), D129.3 (VDD), D130.3 (VDD), D131.3 (VDD), D132.3 (VDD), D133.3 (VDD), D134.3 (VDD), D135.3 (VDD), D136.3 (VDD), D137.3 (VDD), D138.3 (VDD), D139.3 (VDD), D140.3 (VDD), D141.3 (VDD), D142.3 (VDD), D143.3 (VDD), D144.3 (VDD), D145.3 (VDD), D146.3 (VDD), D147.3 (VDD), D148.3 (VDD), D149.3 (VDD), D150.3 (VDD), D151.3 (VDD), D152.3 (VDD), D153.3 (VDD), D154.3 (VDD), D155.3 (VDD), D156.3 (VDD), D157.3 (VDD), D158.3 (VDD), D159.3 (VDD), D160.3 (VDD), D161.3 (VDD), D162.3 (VDD), D163.3 (VDD), D164.3 (VDD), D165.3 (VDD), D166.3 (VDD), D167.3 (VDD), D168.3 (VDD), D169.3 (VDD), D170.3 (VDD), D171.3 (VDD), D172.3 (VDD), D173.3 (VDD), D174.3 (VDD), D175.3 (VDD), D176.3 (VDD), D177.3 (VDD), D178.3 (VDD), D179.3 (VDD), D180.3 (VDD), D181.3 (VDD), D182.3 (VDD), D183.3 (VDD), D184.3 (VDD), D185.3 (VDD), D186.3 (VDD), D187.3 (VDD), D188.3 (VDD), D189.3 (VDD), D190.3 (VDD), D191.3 (VDD), D192.3 (VDD), D193.3 (VDD), D194.3 (VDD), D195.3 (VDD), D196.3 (VDD), D197.3 (VDD), D198.3 (VDD), D199.3 (VDD), D200.3 (VDD), D201.3 (VDD), D202.3 (VDD), D203.3 (VDD), D204.3 (VDD), D205.3 (VDD), D206.3 (VDD), D207.3 (VDD), D208.3 (VDD), D209.3 (VDD), D210.3 (VDD), D211.3 (VDD), D212.3 (VDD), D213.3 (VDD), D214.3 (VDD), D215.3 (VDD), D216.3 (VDD), D217.3 (VDD), D218.3 (VDD), D219.3 (VDD), D220.3 (VDD), D221.3 (VDD), D222.3 (VDD), D223.3 (VDD), D224.3 (VDD), D225.3 (VDD), D226.3 (VDD), D227.3 (VDD), D228.3 (VDD), J4.1, Q2.3 (D), U5.5 (VCC)
VSYS: C3.1, C4.1, D1.1 (K), Q1.2 (S), Q2.2 (S), R18.1, U4.1 (VIN), U4.3 (EN)

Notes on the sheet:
Per-pixel decoupling, 100 nF X7R 0402
Reset, BOOT / user buttons, status LED, test pads
Power path: switch, load sharing, 3V3 LDO, VBAT sense
Data level shifter 3.3 V -> VLED
1S Li-Po charger (MCP73831, 500 mA) + battery connector
Pixel chain (LED_DIN -> LED_MID)
Chain-out pads (more pixels / debug)
I2S MEMS microphone (ICS-43434, bottom port)
VLED bulk capacitance (at the matrix feed)
Pixel chain (LED_MID -> LED_DOUT)
Module decoupling (at the 3V3 pad)
ESP32-C3-WROOM-02 (4 MB flash, Wi-Fi + BLE 5, PCB antenna)
USB-C receptacle, CC pull-downs + sense, ESD
VLED high-side switch

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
